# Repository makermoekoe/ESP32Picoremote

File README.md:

# ESP32PicoD4_TFT_Remote

</a>

WiFi remote based on ESP32 Pico D4 MCU and a beautiful 160x80 pixels mini TFT display. Additionally there is a I2C temperature & humidity sensor as well as an accelerometer on board.

Assembling video is on my [Youtube](https://youtu.be/5vRy--YCx7k).

The power latching circuit ensures that the ESP32 Pico D4 don't need to be in deep sleep mode while in OFF state. This puts it down to around 3µA during 'sleep', due to the battery protection. It can be woke up only by the middle button. The battery protection occupies reverse voltage protection through the mosfet. Overdischarge voltage of the XB5353A is 2.4volts, which is only for safety reasons. The battery voltage should always be checked with the voltage divider, which gives you an estimation of the battery state.

Main components are:
- ESP32 Pico D4
- CP2102N USB to serial bridge
- 160x80px ST7735 13pin TFT display
- HDC1080 temperature and humidity sensors
- LIS3DHTR accelerometer
- WS2812 LEDs
- XB5353A battery protection
- SE7401U polarity
- MCP73831 charging
- RT9193 regulator
- Molex 3D antenna

## Circuit & PCB

`pico32_remote_v1.0` was the initial schematic of this PCB. Unfortunately it occupies a few mistakes:
- Button two is connected to the ESP32 directly behind the button, which gives `VCC` directly to one of the GPIOs of the MCU - meh. The 1k resistor should be between the pulldown and the button.
- Furthermore the footprint of the LIS3DHTR is mirrored (not visible in the schematics).
- Last but not least the `VUSB` of the USB-C connector and the power selection circuit wasn't connected properly because the VUSB on one side was just a label and not the name of connection itself - shame on me.

All these mistakes are fixed in version 1.1. Additionally I have added a USB activation diode, which enables the latching circuit ones a USB cable is plugged into the board. This is nice to have if you want to visualize battery charging. Another advantage is that one of the buttons don't have to be pressed during firmware upload.

## Code

Check out the code in the 'code' section. It is used in PlatformIO, but can be shifted to Arduino IDE easily. The code is exactly the same.

The ST7735 display can be used easily with the [TFT_eSPI library](https://github.com/Bodmer/TFT_eSPI) by Bodmer. This library comes with a `User_Setup.h` to setup the dedicated display you are using. I have attached this file for this specific board in the code section of this repo.

Another nice library to play little GIFs on that tiny display is the [AnimatedGIF library](https://github.com/bitbank2/AnimatedGIF) by Larry Bank. He shared a nice tool for converting GIFs to a code array as well.

## Milled case

It is not yet optimized but the bottom part is looking great. The top part should move left and right while pushing the buttons, unfortunately it doesn't due to the small holes in PCB and bottom part. An easy solution would be to use two elongated holes in the top part (the screw heads would be visible on the top part).

When you have questions then feel free to ask.

Have fun! :)

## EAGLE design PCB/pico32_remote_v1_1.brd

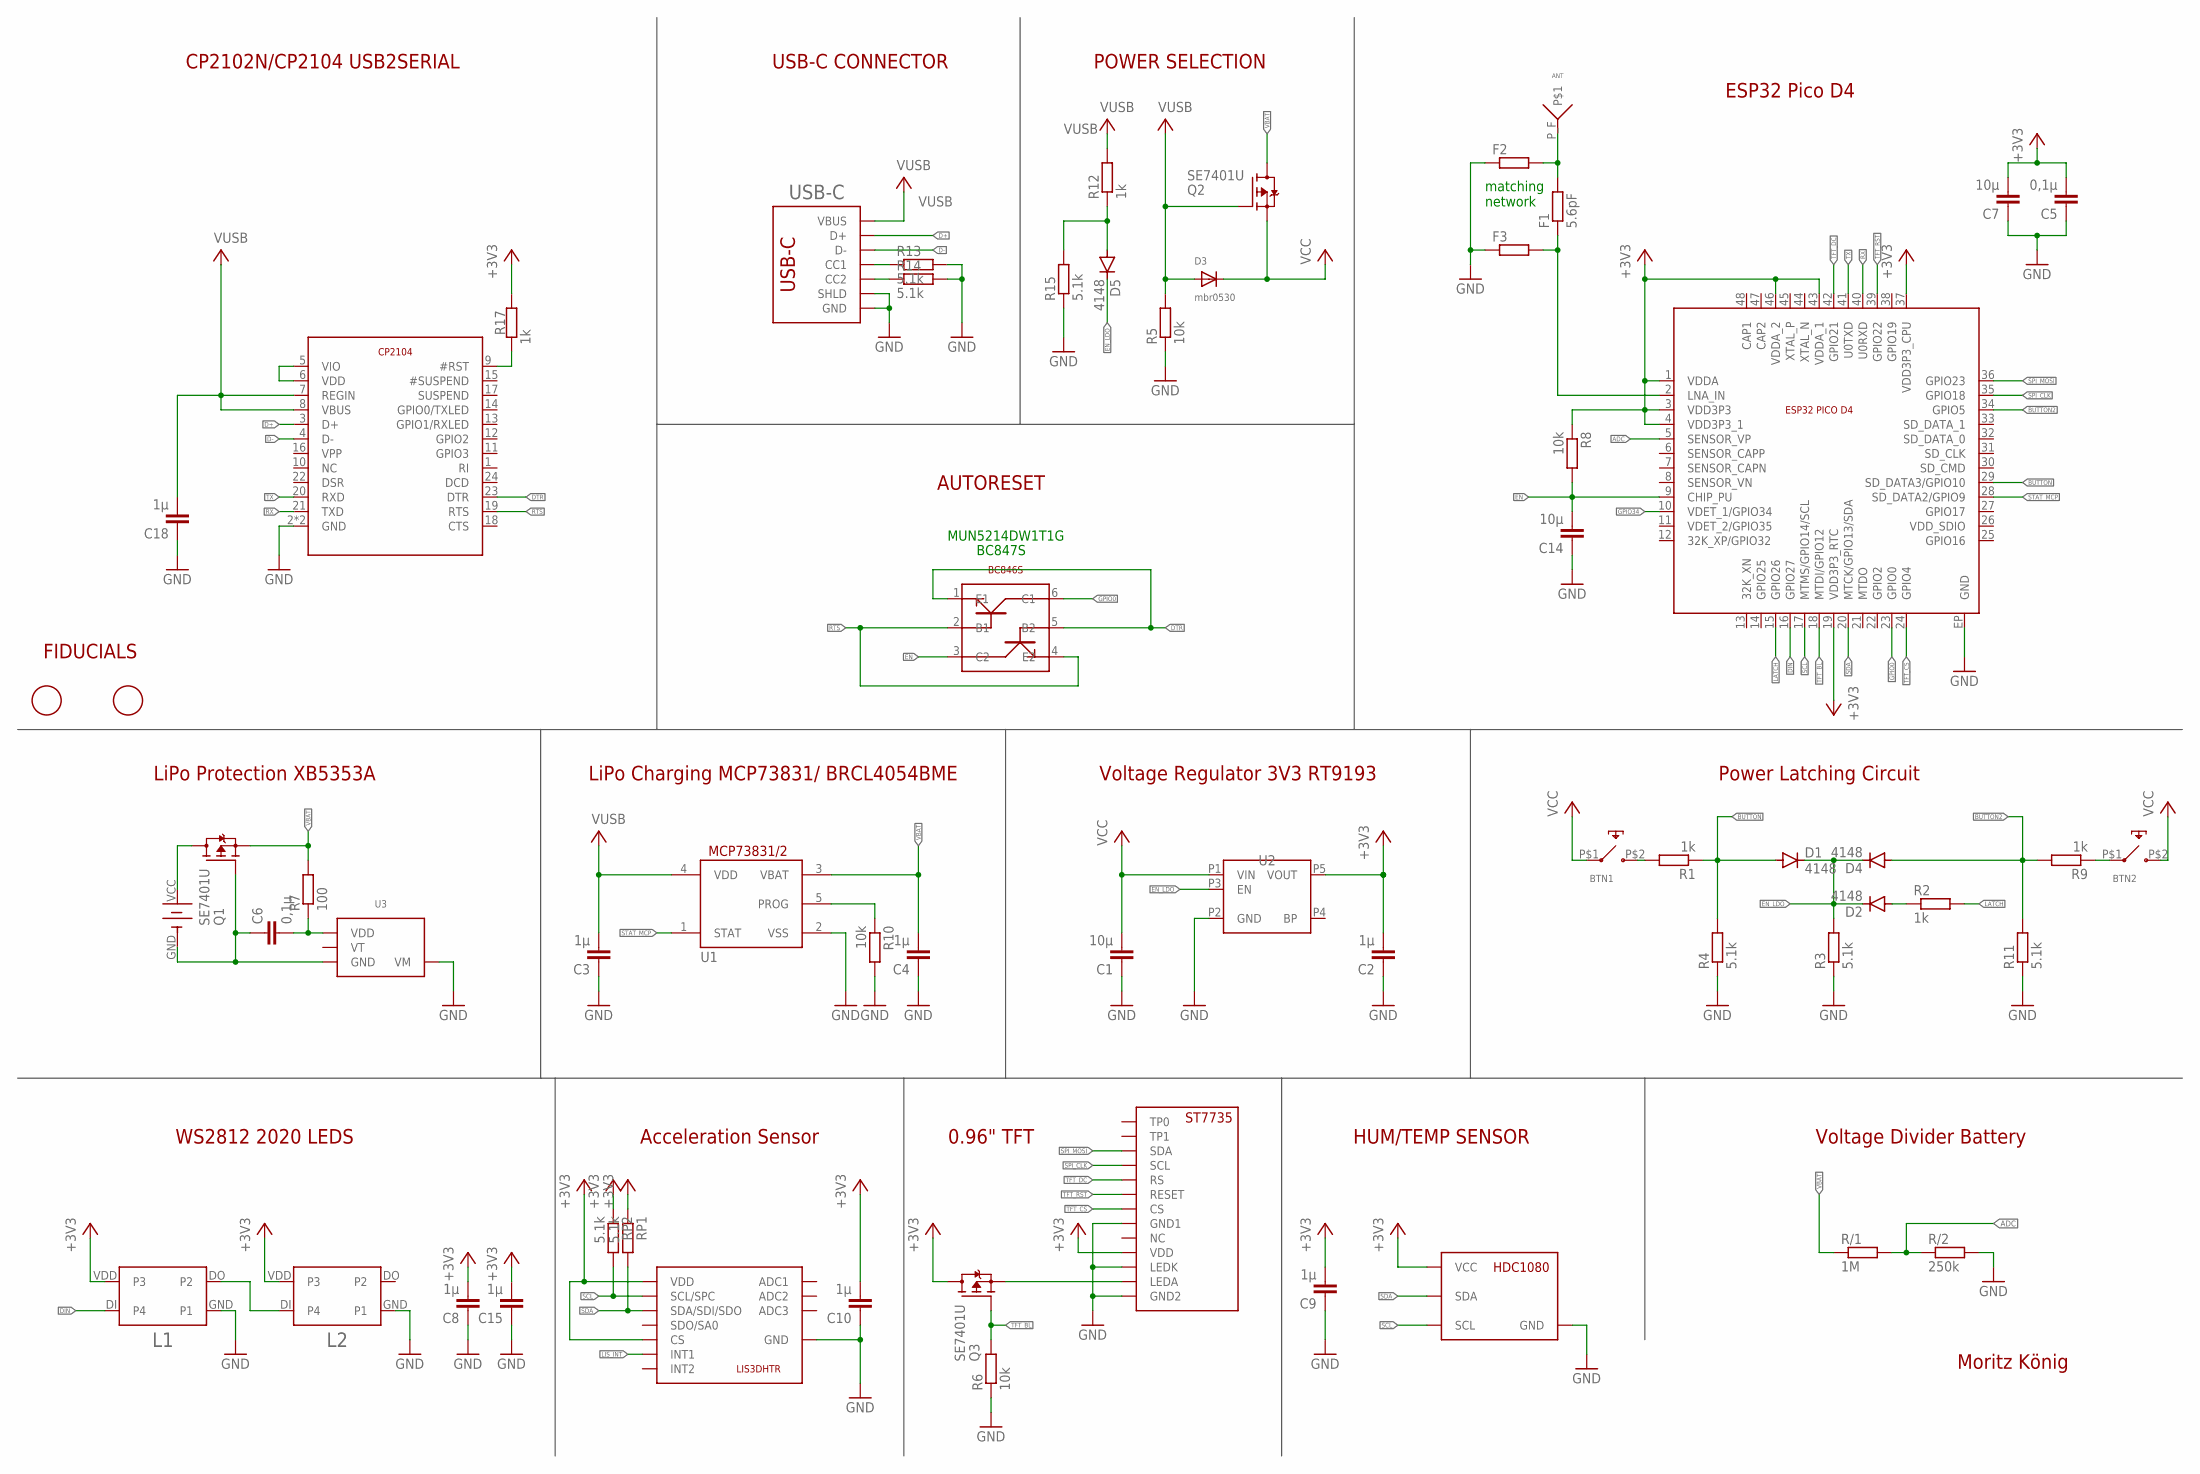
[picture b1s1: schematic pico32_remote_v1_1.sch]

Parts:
ANT: MOLEX_ANT_3D
BTN1, BTN2: BUTTON_6X6_SILICON; BUTTON_SILICON
C1, C7: 10µ; C0603
C2: 1µ; C0603
C3, C4, C8, C9, C10, C15, C18: 1µ; R0402
C5: 0,1µ; C0603
C6: 0,1µ; R0402
C14: 10µ; C0402K
D1, D2, D4, D5: 4148; SOD523
D3: mbr0530; SOD-123FL
ESP32: ESP32_PICO_D4_LP; QFN-48_LONG
F1: 5.6pF; R0402
F2, F3: R-EU-0402-WOKEEPOUT; R0402
L1, L2: WS2812_2020
Q1, Q2, Q3: SE7401U; SOT323
R1, R2, R9, R12, R17: 1k; R0402
R3, R4, R11, R13, R14, R15: 5.1k; R0402
R5, R6, R8, R10: 10k; R0402
R7: 100; R0402
R/1: 1M; R0402
R/2: 250k; R0402
RP1, RP2: 5.1k; R0402
U1: BRCL4054BME; SOT23-5L
U2: RT9193_SC70-5; SC-70-5
U3: XB5353A; SOT23-5
U4: LIS3DHTR; LGA_16_LIS3DHTR
U5: CP2102N; QFN24-4X4
U6: MUN5214DW1T1G; SOT363
U7: HDC1080; WSON08_HDC1080
U$2: 2450_BATTERYHOLDER_SMD
U$4: ST7735_096TFT_TWISTED
U$6, U$7: FIDUCIAL; FIDUCIAL_1MM
USB-C: USB_C_C393939; USBC_C393939

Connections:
+3V3: C2.2, C5.2, C7.2, C8.2, C9.2, C10.2, C15.2, ESP32.1 (VDDA), ESP32.3 (VDD3P3), ESP32.4 (VDD3P3_1), ESP32.19 (VDD3P3_RTC), ESP32.37 (VDD3P3_CPU), ESP32.43 (VDDA_1), ESP32.46 (VDDA_2), L1.VDD (P3), L2.VDD (P3), Q3.3 (D), R8.1, R17.2, RP1.1, RP2.1, U2.P5 (VOUT), U4.P$1 (VDD), U4.P$8 (CS), U4.P$14 (VDD), U7.P5 (VCC), U$4.P10 (VDD)
ADC: ESP32.5 (SENSOR_VP), R/1.2, R/2.1
ANTENNA1: ANT.P_F, F1.2, F2.2
BUTTON: D1.A, ESP32.29 (SD_DATA3/GPIO10), R1.1, R4.2
BUTTON2: D4.A, ESP32.34 (GPIO5), R9.2, R11.2
D+: U5.3 (D+), USB-C.A6 (D+), USB-C.B6 (D+)
D-: U5.4 (D-), USB-C.A7 (D-), USB-C.B7 (D-)
DIN: ESP32.16 (GPIO27), L1.DI (P4)
DTR: U5.23 (DTR), U6.1 (E1), U6.5 (B2)
EN: C14.2, ESP32.9 (CHIP_PU), R8.2, U6.3 (C2)
EN_LDO: D1.C, D2.C, D4.C, D5.C, R3.2, U2.P3 (EN)
GND: C1.1, C2.1, C3.1, C4.1, C5.1, C7.1, C8.1, C9.1, C10.1, C14.1, C15.1, C18.1, ESP32.EP (GND), F2.1, F3.1, L1.GND (P1), L2.GND (P1), R3.1, R4.1, R5.1, R6.1, R10.2, R11.1, R13.2, R14.2, R15.1, R/2.2, U1.2 (VSS), U2.P2 (GND), U3.4 (VM), U3.5 (VM), U4.P$5 (GND), U4.P$10 (GND), U4.P$12 (GND), U5.2 (GND), U5.EXP (GND), U7.P2 (GND), U$4.P8 (GND1), U$4.P11 (LEDK), U$4.P13 (GND2), USB-C.A1B12 (GND), USB-C.B1A12 (GND), USB-C.S1 (SHLD), USB-C.S2 (SHLD), USB-C.S3 (SHLD), USB-C.S4 (SHLD)
GPIO0: ESP32.23 (GPIO0), U6.6 (C1)
GPIO34: ESP32.10 (VDET_1/GPIO34)
LATCH: ESP32.15 (GPIO26), R2.2
LIS_INT: U4.P$11 (INT1)
unnamed: U5.5 (VIO), U5.6 (VDD)
unnamed: BTN2.P$1 (P1), R9.1
unnamed: Q3.2 (S), U$4.P12 (LEDA)
unnamed: ESP32.2 (LNA_IN), F1.1, F3.2
unnamed: C6.2, R7.1, U3.3 (VDD)
unnamed: D5.A, R12.1, R15.2
unnamed: C6.1, Q1.1 (G), U3.2 (GND), U$2.GND
unnamed: Q1.3 (D), U$2.VCC
unnamed: L1.DO (P2), L2.DI (P4)
unnamed: BTN1.P$2 (P2), R1.2
unnamed: D2.A, R2.1
unnamed: R14.1, USB-C.B5 (CC2)
unnamed: R10.1, U1.5 (PROG)
unnamed: R13.1, USB-C.A5 (CC1)
unnamed: R17.1, U5.9 (#RST)
RTS: U5.19 (RTS), U6.2 (B1), U6.4 (E2)
RX: ESP32.40 (U0RXD), U5.21 (TXD)
SCL: ESP32.17 (MTMS/GPIO14/SCL), RP2.2, U4.P$4 (SCL/SPC), U7.P6 (SCL)
SDA: ESP32.20 (MTCK/GPIO13/SDA), RP1.2, U4.P$6 (SDA/SDI/SDO), U7.P1 (SDA)
SPI_CLK: ESP32.35 (GPIO18), U$4.P4 (SCL)
SPI_MOSI: ESP32.36 (GPIO23), U$4.P3 (SDA)
STAT_MCP: ESP32.28 (SD_DATA2/GPIO9), U1.1 (STAT)
TFT_BL: ESP32.18 (MTDI/GPIO12), Q3.1 (G), R6.2
TFT_CS: ESP32.24 (GPIO4), U$4.P7 (CS)
TFT_DC: ESP32.42 (GPIO21), U$4.P5 (RS)
TFT_RST: ESP32.39 (GPIO22), U$4.P6 (RESET)
TX: ESP32.41 (U0TXD), U5.20 (RXD)
VBAT: C4.2, Q1.2 (S), Q2.3 (D), R7.2, R/1.1, U1.3 (VBAT)
VCC: BTN1.P$1 (P1), BTN2.P$2 (P2), C1.2, D3.C, Q2.2 (S), U2.P1 (VIN)
VUSB: C3.2, C18.2, D3.A, Q2.1 (G), R5.2, R12.2, U1.4 (VDD), U5.7 (REGIN), U5.8 (VBUS), USB-C.A4B9 (VBUS), USB-C.B4A9 (VBUS)

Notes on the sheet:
Moritz König
Voltage Divider Battery
LiPo Protection XB5353A
LiPo Charging MCP73831/ BRCL4054BME
Voltage Regulator 3V3 RT9193
Power Latching Circuit
WS2812 2020 LEDS
BC847S
USB-C CONNECTOR
CP2102N/CP2104 USB2SERIAL
AUTORESET
MUN5214DW1T1G
Acceleration Sensor
ESP32 Pico D4
POWER SELECTION
HUM/TEMP SENSOR
0.96" TFT
FIDUCIALS
matching network

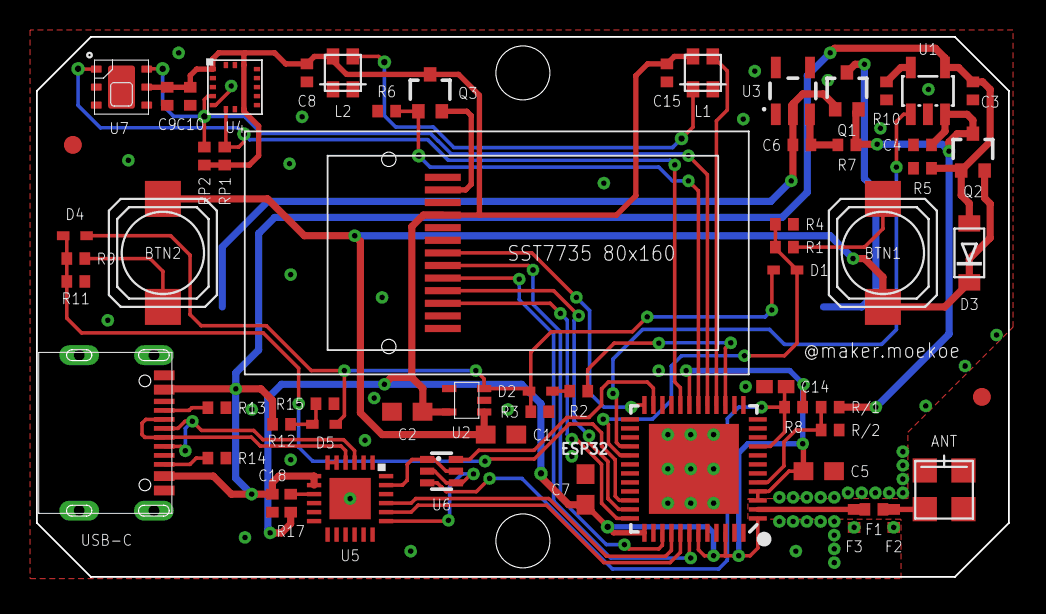
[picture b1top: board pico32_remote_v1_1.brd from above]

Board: 2 copper layers, 54.0 x 30.0 mm, 62 parts (1 on the bottom side), 44 nets.

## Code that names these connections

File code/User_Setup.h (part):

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//
// ##################################################################################

// If a backlight control signal is available then define the TFT_BL pin in Section 2
// below. The backlight will be turned ON when tft.begin() is called, but the library
// needs to know if the LEDs are ON with the pin HIGH or LOW. If the LEDs are to be
// driven with a PWM signal or turned OFF/ON then this must be handled by the user
// sketch. e.g. with digitalWrite(TFT_BL, LOW);

//#define TFT_BL   12            // LED back-light control pin
#define TFT_BACKLIGHT_ON LOW  // Level to turn ON back-light (HIGH or LOW)


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// The DC (Data Command) pin may be labelled AO or RS (Register Select)
//
// With some displays such as the ILI9341 the TFT CS pin can be connected to GND if no more
// SPI devices (e.g. an SD Card) are connected, in this case comment out the #define TFT_CS
// line below so it is NOT defined. Other displays such at the ST7735 require the TFT CS pin
// to be toggled during setup, so in these cases the TFT_CS line must be defined and connected.
//
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// ###### EDIT THE PIN NUMBERS IN THE LINES FOLLOWING TO SUIT YOUR ESP8266 SETUP ######

// For NodeMCU - use pin numbers in the form PIN_Dx where Dx is the NodeMCU pin designation
#define TFT_CS   4  // Chip select control pin D8
#define TFT_DC   21  // Data Command control pin
#define TFT_RST  22  // Reset pin (could connect to NodeMCU RST, see next line)
//#define TFT_RST  -1    // Set TFT_RST to -1 if the display RESET is connected to NodeMCU RST or 3.3V

//#define TFT_BL PIN_D1  // LED back-light (only for ST7789 with backlight control pin)

//#define TOUCH_CS PIN_D2     // Chip select pin (T_CS) of touch screen

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//#define TFT_SPI_OVERLAP

// In ESP8266 overlap mode the TFT chip select MUST connect to pin D3
//#define TFT_CS   PIN_D3
//#define TFT_DC   PIN_D5  // Data Command control pin
//#define TFT_RST  PIN_D4  // Reset pin (could connect to NodeMCU RST, see next line)
//#define TFT_RST  -1  // Set TFT_RST to -1 if the display RESET is connected to NodeMCU RST or 3.3V


// ###### EDIT THE PIN NUMBERS IN THE LINES FOLLOWING TO SUIT YOUR ESP32 SETUP   ######
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#define TFT_MISO 19
#define TFT_MOSI 23
#define TFT_SCLK 18
//#define TFT_CS   15  // Chip select control pin
//#define TFT_DC    2  // Data Command control pin
//#define TFT_RST   4  // Reset pin (could connect to RST pin)
//#define TFT_RST  -1  // Set TFT_RST to -1 if display RESET is connected to ESP32 board RST

// For ESP32 Dev board (only tested with GC9A01 display)
// The hardware SPI can be mapped to any pins

//#define TFT_MOSI 15 // In some display driver board, it might be written as "SDA" and so on.
//#define TFT_SCLK 14
//#define TFT_CS   5  // Chip select control pin
//#define TFT_DC   27  // Data Command control pin
//#define TFT_RST  33  // Reset pin (could connect to Arduino RESET pin)
//#define TFT_BL   22  // LED back-light

//#define TOUCH_CS 21     // Chip select pin (T_CS) of touch screen

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//#define TFT_MISO 19
//#define TFT_MOSI 23
//#define TFT_SCLK 18
//#define TFT_CS   14  // Chip select control pin
//#define TFT_DC   27  // Data Command control pin
//#define TFT_RST  33  // Reset pin (could connect to Arduino RESET pin)
//#define TFT_BL   32  // LED back-light (required for M5Stack)

// ######       EDIT THE PINs BELOW TO SUIT YOUR ESP32 PARALLEL TFT SETUP        ######

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//#define TFT_PARALLEL_8_BIT

// The ESP32 and TFT the pins used for testing are:
//#define TFT_CS   33  // Chip select control pin (library pulls permanently low
//#define TFT_DC   15  // Data Command control pin - must use a pin in the range 0-31
//#define TFT_RST  32  // Reset pin, toggles on startup

//#define TFT_WR    4  // Write strobe control pin - must use a pin in the range 0-31
//#define TFT_RD    2  // Read strobe control pin
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//#define TFT_SCLK PB13

// Can use Ardiuno pin references, arbitrary allocation, TFT_eSPI controls chip select
//#define TFT_CS   D5 // Chip select control pin to TFT CS
//#define TFT_DC   D6 // Data Command control pin to TFT DC (may be labelled RS = Register Select)
//#define TFT_RST  D7 // Reset pin to TFT RST (or RESET)
// OR alternatively, we can use STM32 port reference names PXnn
//#define TFT_CS   PE11 // Nucleo-F767ZI equivalent of D5
//#define TFT_DC   PE9  // Nucleo-F767ZI equivalent of D6
//#define TFT_RST  PF13 // Nucleo-F767ZI equivalent of D7

//#define TFT_RST  -1   // Set TFT_RST to -1 if the display RESET is connected to processor reset
                        // Use an Arduino pin for initial testing as connecting to processor reset
                        // may not work (pulse too short at power up?)

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
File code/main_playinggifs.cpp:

#include <Arduino.h>
#include <driver/dac.h>
#include <FastLED.h>
#include <Wire.h>
#include "ClosedCube_HDC1080.h"

#include <AnimatedGIF.h>
#include <TFT_eSPI.h>
#include <SPI.h>
#include "../test_images/moekoe2.h"
//#include "../test_images/badgers.h"
//#include "../test_images/homer.h"
//#include "../test_images/homer_tiny.h"
//#include "../test_images/pattern.h"
//#include <Adafruit_LIS3DH.h>
//#include <Adafruit_Sensor.h>

ClosedCube_HDC1080 hdc;
TFT_eSPI tft = TFT_eSPI();
//Adafruit_LIS3DH lis = Adafruit_LIS3DH();


#define DISPLAY_WIDTH 160
#define DISPLAY_HEIGHT 80
AnimatedGIF gif;

#define NORMAL_SPEED
#define GIF_IMAGE1 moekoe2

struct box {
  uint8_t left,top,width,height;
  uint32_t color,color_in;
  uint8_t border,radius;

  int left_in(){return left + border;}
  int top_in(){return top + border;}
  int width_in(){return width - 2*border;}
  int height_in(){return height - 2*border;}
};

box bbox_left = {1,2,2,76,TFT_WHITE,TFT_BLUE,0,2};
box bbox_right = {157,2,2,76,TFT_WHITE,TFT_BLUE,0,2};

box center = {bbox_left.left+bbox_left.width,0,bbox_right.left-(bbox_left.left+bbox_left.width),80,0,0,0,0};

const int btn1 = 25;
const int btn2 = 5;
const int latch = 26;
const int led_pin = 27;
const int tft_bl = 12;
const int stat_mcp = 9;

#define NUM_LEDS 2
CRGB leds[NUM_LEDS];

bool ostate_left, state_left = false;
bool ostate_right, state_right = false;

void draw_buttons(bool left_pressed, bool right_pressed){
  tft.fillRect(bbox_left.left, bbox_left.top, bbox_left.width, bbox_left.height, TFT_BLACK);
  tft.fillRect(bbox_right.left, bbox_right.top, bbox_right.width, bbox_right.height, TFT_BLACK);

  tft.fillRoundRect(bbox_left.left, bbox_left.top, bbox_left.width, bbox_left.height, bbox_left.radius, bbox_left.color);
  tft.fillRoundRect(bbox_right.left, bbox_right.top, bbox_right.width, bbox_right.height, bbox_right.radius, bbox_right.color);

  if(left_pressed){
    tft.fillRoundRect(bbox_left.left_in(), bbox_left.top_in(), bbox_left.width_in(), bbox_left.height_in(), bbox_left.radius, bbox_left.color_in);
  }
  if(right_pressed){
    tft.fillRoundRect(bbox_right.left_in(), bbox_right.top_in(), bbox_right.width_in(), bbox_right.height_in(), bbox_right.radius, bbox_right.color_in);
  }
}

int read_buttons(bool &b1, bool &b2, bool upd_tft, bool upd_leds){
  b1 = digitalRead(btn2);
  b2 = digitalRead(btn1);
  if(upd_tft && (ostate_left != state_left || ostate_right != state_right)){
    draw_buttons(state_left, state_right);
    ostate_left = state_left;
    ostate_right = state_right;
  }
  if(upd_leds){
    leds[1] = CRGB(0,b1*150,0);
    leds[0] = CRGB(0,0,b2*150);
    FastLED.show();
  }
}

void update_hdc(){
  float temp_hdc = hdc.readTemperature();
  float hum_hdc = hdc.readHumidity();
  tft.fillRect(center.left, center.top, center.width, center.height, TFT_BLACK);
  tft.setTextColor(TFT_BLUE, TFT_BLACK);

  tft.setTextDatum(MC_DATUM);
  tft.drawString((String(temp_hdc) + "C"),50,40,2);
  tft.setTextDatum(MC_DATUM);
  tft.drawString((String(hum_hdc) + "%"),110,40,2);
}


#define BUFFER_SIZE 256
uint16_t usTemp[1][BUFFER_SIZE];
bool     dmaBuf = 0;
  
void GIFDraw(GIFDRAW *pDraw)
{
  uint8_t *s;
  uint16_t *d, *usPalette;
  int x, y, iWidth, iCount;

  // Displ;ay bounds chech and cropping
  iWidth = pDraw->iWidth;
  if (iWidth + pDraw->iX > DISPLAY_WIDTH)
    iWidth = DISPLAY_WIDTH - pDraw->iX;
  usPalette = pDraw->pPalette;
  y = pDraw->iY + pDraw->y; // current line
  if (y >= DISPLAY_HEIGHT || pDraw->iX >= DISPLAY_WIDTH || iWidth < 1)
    return;

  // Old image disposal
  s = pDraw->pPixels;
  if (pDraw->ucDisposalMethod == 2) // restore to background color
  {
    for (x = 0; x < iWidth; x++)
    {
      if (s[x] == pDraw->ucTransparent)
        s[x] = pDraw->ucBackground;
    }
    pDraw->ucHasTransparency = 0;
  }

  // Apply the new pixels to the main image
  if (pDraw->ucHasTransparency) // if transparency used
  {
    uint8_t *pEnd, c, ucTransparent = pDraw->ucTransparent;
    pEnd = s + iWidth;
    x = 0;
    iCount = 0; // count non-transparent pixels
    while (x < iWidth)
    {
      c = ucTransparent - 1;
      d = &usTemp[0][0];
      while (c != ucTransparent && s < pEnd && iCount < BUFFER_SIZE )
      {
        c = *s++;
        if (c == ucTransparent) // done, stop
        {
          s--; // back up to treat it like transparent
        }
        else // opaque
        {
          *d++ = usPalette[c];
          iCount++;
        }
      } // while looking for opaque pixels
      if (iCount) // any opaque pixels?
      {
        // DMA would degrtade performance here due to short line segments
        tft.setAddrWindow(pDraw->iX + x, y, iCount, 1);
        tft.pushPixels(usTemp, iCount);
        x += iCount;
        iCount = 0;
      }
      // no, look for a run of transparent pixels
      c = ucTransparent;
      while (c == ucTransparent && s < pEnd)
      {
        c = *s++;
        if (c == ucTransparent)
          x++;
        else
          s--;
      }
    }
  }
  else
  {
    s = pDraw->pPixels;

    // Unroll the first pass to boost DMA performance
    // Translate the 8-bit pixels through the RGB565 palette (already byte reversed)
    if (iWidth <= BUFFER_SIZE)
      for (iCount = 0; iCount < iWidth; iCount++) usTemp[dmaBuf][iCount] = usPalette[*s++];
    else
      for (iCount = 0; iCount < BUFFER_SIZE; iCount++) usTemp[dmaBuf][iCount] = usPalette[*s++];

#ifdef USE_DMA // 71.6 fps (ST7796 84.5 fps)
    tft.dmaWait();
    tft.setAddrWindow(pDraw->iX, y, iWidth, 1);
    tft.pushPixelsDMA(&usTemp[dmaBuf][0], iCount);
    dmaBuf = !dmaBuf;
#else // 57.0 fps
    tft.setAddrWindow(pDraw->iX, y, iWidth, 1);
    tft.pushPixels(&usTemp[0][0], iCount);
#endif

    iWidth -= iCount;
    // Loop if pixel buffer smaller than width
    while (iWidth > 0)
    {
      // Translate the 8-bit pixels through the RGB565 palette (already byte reversed)
      if (iWidth <= BUFFER_SIZE)
        for (iCount = 0; iCount < iWidth; iCount++) usTemp[dmaBuf][iCount] = usPalette[*s++];
      else
        for (iCount = 0; iCount < BUFFER_SIZE; iCount++) usTemp[dmaBuf][iCount] = usPalette[*s++];

#ifdef USE_DMA
      tft.dmaWait();
      tft.pushPixelsDMA(&usTemp[dmaBuf][0], iCount);
      dmaBuf = !dmaBuf;
#else
      tft.pushPixels(&usTemp[0][0], iCount);
#endif
      iWidth -= iCount;
    }
  }
} /* GIFDraw() */

void play_gif1(){
  if (gif.open((uint8_t *)GIF_IMAGE1, sizeof(GIF_IMAGE1), GIFDraw)) {
    Serial.printf("Successfully opened GIF; Canvas size = %d x %d\n", gif.getCanvasWidth(), gif.getCanvasHeight());
    tft.startWrite(); // The TFT chip slect is locked low
    while (gif.playFrame(true, NULL)) {
      yield();
    }
    gif.close();
    tft.endWrite(); // Release TFT chip select for other SPI devices
  }
}


void setup() {
  pinMode(latch,OUTPUT);
  digitalWrite(latch,HIGH);

  dac_output_disable(DAC_CHANNEL_1);

  pinMode(btn1,INPUT);
  pinMode(btn2,INPUT);
  Serial.begin(115200);
  Serial.println("start");

  pinMode(tft_bl,OUTPUT);
  digitalWrite(tft_bl,HIGH);

  Wire.begin(13,14);

  FastLED.addLeds<WS2812, led_pin, GRB>(leds, NUM_LEDS);
  FastLED.setBrightness(200);
  delay(1);
  for (int i = 0; i < NUM_LEDS; i++) leds[i] = CRGB(150, 0, 0);
  FastLED.show();

  hdc.begin(0x40);

  tft.init();
  tft.fillScreen(TFT_BLACK);
  tft.setRotation(3);

  gif.begin(BIG_ENDIAN_PIXELS);

  digitalWrite(tft_bl,LOW);

  play_gif1();

  //draw_buttons(0,0);
}



unsigned long t = millis();
unsigned long t_both_btn_pressed = 0;



void loop() {
  play_gif1();

  read_buttons(state_left, state_right, true, true);
  if(state_left && state_right){
    if(millis() > t_both_btn_pressed + 1000){
      //shut down device
      for (int i = 0; i < NUM_LEDS; i++) leds[i] = CRGB(150, 0, 0);
      FastLED.show();
      digitalWrite(latch,LOW);
      delay(200);
      while(digitalRead(btn1)) delay(100);
    }
  }
  else if(state_left){
    
  }
  else if(state_right){

  }
  else{
    t_both_btn_pressed = millis();
  }

  delay(10);

  /*if(millis() > t + 1000){
    update_hdc();
    t = millis();
  }*/
  
}

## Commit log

2021-04-18 added code and stuff
2021-04-18 added case v1.0
2021-04-18 typos
2021-04-23 added video to the description
